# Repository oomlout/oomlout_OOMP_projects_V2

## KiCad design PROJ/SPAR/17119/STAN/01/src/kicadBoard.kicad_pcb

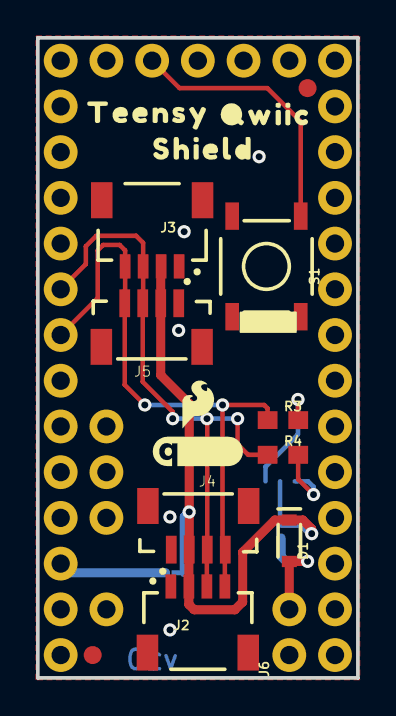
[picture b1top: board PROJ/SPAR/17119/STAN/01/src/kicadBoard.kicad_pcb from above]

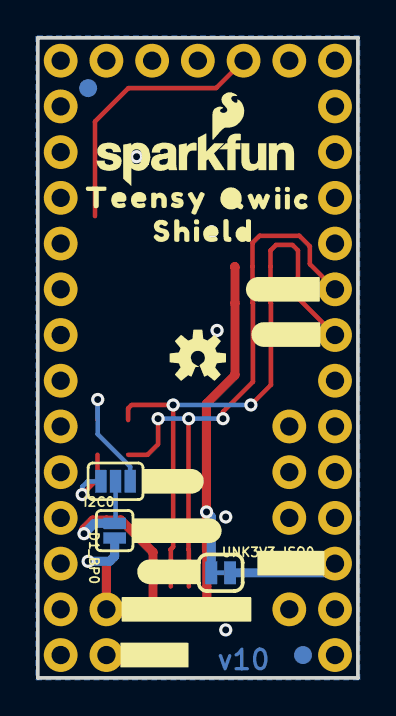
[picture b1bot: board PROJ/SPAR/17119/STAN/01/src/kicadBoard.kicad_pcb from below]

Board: 2 copper layers, 17.8 x 35.6 mm, 38 parts (18 on the bottom side), 9 nets.

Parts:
D1: 3A/10V/280mV; SOD-323
D1_BP0: SMT-JUMPER_2_NO_SILK
FD1, FD2, FD3, FD4: FIDUCIAL1X2; FIDUCIAL-1X2
FRAME1: FRAME-LETTER; CREATIVE_COMMONS
I2C0: JUMPER-SMT_3_NO_SILK; SMT-JUMPER_3_NO_SILK
J1: TEENSY; TEENSY_NOSILK
J2, J3: QWIIC_RA; JST04_1MM_RA
J4, J5: QWIIC_Vertical; JST04_1MM_VERT
J6: ALT PWR; 1X02_NO_SILK
LOGO1: SFE_LOGO_NAME_FLAME.1_INCH; SFE_LOGO_NAME_FLAME_.1
LOGO2: SFE_LOGO_FLAME.1_INCH; SFE_LOGO_FLAME_.1
LOGO3: OSHW-LOGOS; OSHW-LOGO-S
LOGO4: QWIIC_LOGO_5MM; QWIIC_5MM
R3, R4: 4.7k; 0603
S1: SMD_5.2MM; TACTILE_SWITCH_SMD_5.2MM
U$1: #I2C#0
U$2, U$13: TEENSY0
U$3: 3V36
U$4: #D1_BP#0
U$5: #ALT_3V3#0
U$6: #PRG#0
U$7: #GND#0
U$8, U$12: SHIELD0
U$9, U$11: QWIIC0
U$10: #ISO#0
U$15: #3V3#0
U$18: #SDA#0
U$19: #SCL#0
UNK3V3_ISO0: SMT-JUMPER_2_NC_TRACE_SILK

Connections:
3.3V: D1.C, D1_BP0.2, I2C0.2, J2.2, J3.2, J4.2, J5.2, UNK3V3_ISO0.1
GND: J1.AGND, J1.GND, J1.GND1, J2.1, J3.1, J4.1, J5.1, J6.1, S1.3
unnamed: I2C0.3, R4.2
unnamed: I2C0.1, R3.2
unnamed: J1.3V, UNK3V3_ISO0.2
unnamed: D1.A, D1_BP0.1, J6.2
unnamed: J1.PROG, S1.1
SCL: J1.19, J2.4, J3.4, J4.4, J5.4, R3.1
SDA: J1.18, J2.3, J3.3, J4.3, J5.3, R4.1

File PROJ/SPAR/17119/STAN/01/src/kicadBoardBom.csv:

"Id";"Designator";"Package";"Quantity";"Designation";"Supplier and ref";
1;"LOGO2";"SFE_LOGO_FLAME_.1";1;"SFE_LOGO_FLAME.1_INCH";;;
2;"J4,J5";"JST04_1MM_VERT";2;"QWIIC_Vertical";;;
3;"U$9,U$11";"QWIIC0";2;"";;;
4;"U$13,U$2";"TEENSY0";2;"";;;
5;"U$6";"#PRG#0";1;"";;;
6;"J1";"TEENSY_NOSILK";1;"TEENSY";;;
7;"FRAME1";"CREATIVE_COMMONS";1;"FRAME-LETTER";;;
8;"R4,R3";"0603";2;"4.7k";;;
9;"U$8,U$12";"SHIELD0";2;"";;;
10;"U$3";"3V36";1;"";;;
11;"D1";"SOD-323";1;"3A/10V/280mV";;;
12;"J3,J2";"JST04_1MM_RA";2;"QWIIC_RA";;;
13;"LOGO4";"QWIIC_5MM";1;"QWIIC_LOGO_5MM";;;
14;"FD3,FD1,FD2,FD4";"FIDUCIAL-1X2";4;"FIDUCIAL1X2";;;
15;"S1";"TACTILE_SWITCH_SMD_5.2MM";1;"SMD_5.2MM";;;
16;"J6";"1X02_NO_SILK";1;"ALT PWR";;;
17;"U$1";"#I2C#0";1;"";;;
18;"UNK3V3_ISO0";"SMT-JUMPER_2_NC_TRACE_SILK";1;"";;;
19;"U$7";"#GND#0";1;"";;;
20;"LOGO3";"OSHW-LOGO-S";1;"OSHW-LOGOS";;;
21;"U$10";"#ISO#0";1;"";;;
22;"D1_BP0";"SMT-JUMPER_2_NO_SILK";1;"";;;
23;"U$15";"#3V3#0";1;"";;;
24;"LOGO1";"SFE_LOGO_NAME_FLAME_.1";1;"SFE_LOGO_NAME_FLAME.1_INCH";;;
25;"U$18";"#SDA#0";1;"";;;
26;"U$5";"#ALT_3V3#0";1;"";;;
27;"U$19";"#SCL#0";1;"";;;
28;"U$4";"#D1_BP#0";1;"";;;
29;"I2C0";"SMT-JUMPER_3_NO_SILK";1;"JUMPER-SMT_3_NO_SILK";;;

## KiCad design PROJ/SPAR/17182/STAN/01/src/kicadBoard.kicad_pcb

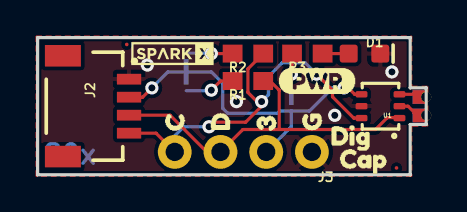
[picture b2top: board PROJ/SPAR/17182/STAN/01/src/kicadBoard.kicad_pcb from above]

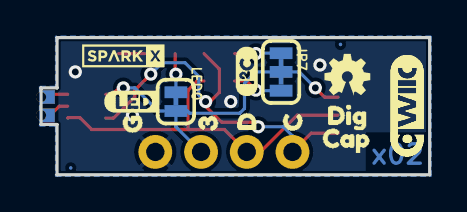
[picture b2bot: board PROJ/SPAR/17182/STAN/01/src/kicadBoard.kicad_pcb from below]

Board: 2 copper layers, 21.6 x 7.6 mm, 36 parts (16 on the bottom side), 10 nets.

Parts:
D1: RED; LED-0603
FRAME1: FRAME-LETTER; CREATIVE_COMMONS
J1: CONN_02_0603; 0603_CASTELLATED
J2: QWIIC_RIGHT_ANGLE; JST04_1MM_RA
J3: PTH; 1X04_NO_SILK
JP1, JP2, JP5, JP6: FIDUCIAL0.2MM; FIDUCIAL-0.2MM
JP7: JUMPER-SMT_3_2-NC_TRACE_SILK; SMT-JUMPER_3_2-NC_TRACE_SILK
LED0: JUMPER-SMT_2_NC_TRACE_SILK; SMT-JUMPER_2_NC_TRACE_SILK
LOGO1: OSHW-LOGOMINI; OSHW-LOGO-MINI
LOGO2: SPECIAL_INSTRUCTIONS-ORDERING; ORDERING_INSTRUCTIONS
R1, R2: 2.2k; 0603
R3: 1k; 0603
U1: NCD2400MDFN; DFN6
U$1: PWR2
U$3, U$7: 32
U$4, U$8: C0
U$5, U$13: D1
U$6, U$14: G3
U$9: I_SUPER2_C-()-03
U$11, U$18: CAP1
U$12, U$16: SPARKX-TINY
U$15: LED0
U$20, U$21: QWIIC_COPYRIGHT_SMALL
U$22, U$23: DIG0

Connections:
3.3V: J2.2, J3.2, JP7.2, LED0.2, U1.4
CN: J1.2, U1.3
CP: J1.1, U1.2
GND: D1.C, J2.1, J3.1, U1.5
unnamed: JP7.3, R1.2
unnamed: JP7.1, R2.2
unnamed: D1.A, R3.1
unnamed: LED0.1, R3.2
SCL: J2.4, J3.4, R2.1, U1.6
SDA: J2.3, J3.3, R1.1, U1.1

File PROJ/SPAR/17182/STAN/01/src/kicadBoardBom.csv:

"Id";"Designator";"Package";"Quantity";"Designation";"Supplier and ref";
1;"LOGO2";"ORDERING_INSTRUCTIONS";1;"SPECIAL_INSTRUCTIONS-ORDERING";;;
2;"J1";"0603_CASTELLATED";1;"CONN_02_0603";;;
3;"U$11,U$18";"CAP1";2;"";;;
4;"J3";"1X04_NO_SILK";1;"PTH";;;
5;"J2";"JST04_1MM_RA";1;"QWIIC_RIGHT_ANGLE";;;
6;"U$13,U$5";"D1";2;"";;;
7;"R2,R1";"0603";2;"2.2k";;;
8;"U$1";"PWR2";1;"";;;
9;"U1";"DFN6";1;"NCD2400MDFN";;;
10;"U$22,U$23";"DIG0";2;"";;;
11;"U$12,U$16";"SPARKX-TINY";2;"";;;
12;"D1";"LED-0603";1;"RED";;;
13;"JP2,JP6,JP1,JP5";"FIDUCIAL-0.2MM";4;"FIDUCIAL0.2MM";;;
14;"U$7,U$3";"32";2;"";;;
15;"R3";"0603";1;"1k";;;
16;"U$14,U$6";"G3";2;"";;;
17;"FRAME1";"CREATIVE_COMMONS";1;"FRAME-LETTER";;;
18;"U$8,U$4";"C0";2;"";;;
19;"LED0";"SMT-JUMPER_2_NC_TRACE_SILK";1;"JUMPER-SMT_2_NC_TRACE_SILK";;;
20;"U$21,U$20";"QWIIC_COPYRIGHT_SMALL";2;"";;;
21;"U$9";"I_SUPER2_C-()-03";1;"";;;
22;"JP7";"SMT-JUMPER_3_2-NC_TRACE_SILK";1;"JUMPER-SMT_3_2-NC_TRACE_SILK";;;
23;"LOGO1";"OSHW-LOGO-MINI";1;"OSHW-LOGOMINI";;;
24;"U$15";"LED0";1;"";;;

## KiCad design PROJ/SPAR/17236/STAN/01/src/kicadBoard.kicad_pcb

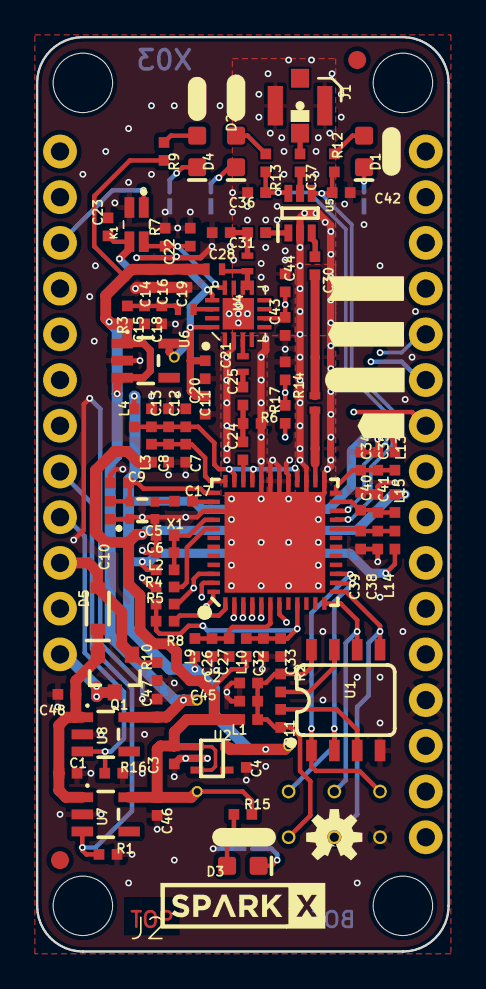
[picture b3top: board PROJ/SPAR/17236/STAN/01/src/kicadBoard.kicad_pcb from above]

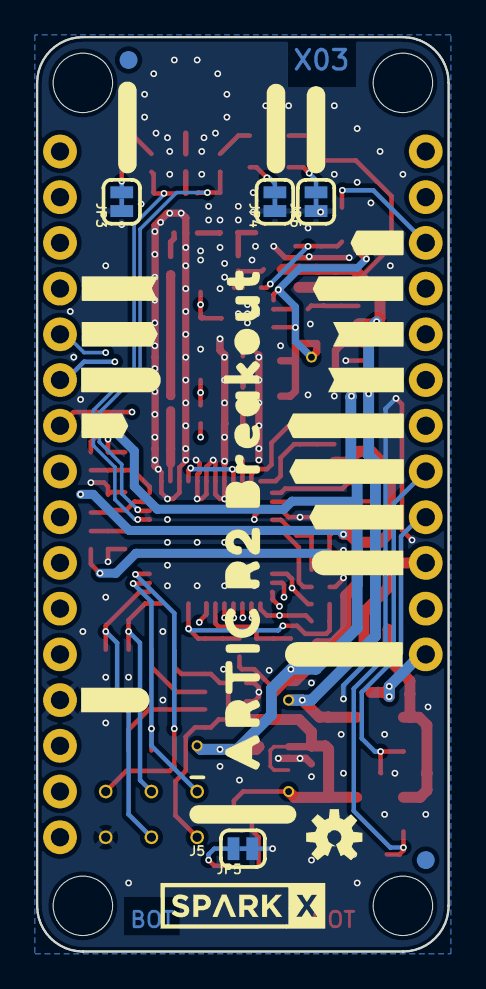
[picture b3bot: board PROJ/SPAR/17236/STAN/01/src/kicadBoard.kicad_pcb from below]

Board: 4 copper layers, 22.9 x 50.8 mm, 144 parts (28 on the bottom side), 65 nets.

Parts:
C1, C15, C16, C20, C44, C46, C47: 2.2uF; 0402-TIGHT
C2, C5, C7, C18, C27, C33, C34, C39, C40: 22pF; 0402-TIGHT
C3, C4, C9, C12: 1.0uF; 0402-TIGHT
C6, C8, C26, C32, C35, C38, C41, C45, C48: 0.1uF; 0402-TIGHT
C10: 47nF; 0402-TIGHT
C11, C19, C21, C22, C23, C24, C25, C30, C31, C36, C37, C42, C43: 100pF; 0402-TIGHT
C13, C14: 10uF; 0402-TIGHT
C17: 1.0nF; 0402-TIGHT
C28: 9.1pF; 0402-TIGHT
C29: 2.4 pF; 0402_MURATA
D1, D2: Yellow; LED-0603
D3, D4: RED; LED-0603
D5: 1A/23V/620mV; SOD-323
FD1, FD2, FD3, FD4: FIDUCIAL1X2; FIDUCIAL-1X2
FRAME1: FRAME-LEDGER; CREATIVE_COMMONS
J1: U.FL
J2: THING_PLUS
J5: Flash Programming; 2X3_TEST_POINTS
JP3, JP4, JP5, JP6: JUMPER-SMT_2_NC_TRACE_SILK; SMT-JUMPER_2_NC_TRACE_SILK
K1: TLP3475R; TLP3475RTPF
L1, L2, L3, L4, L9, L10, L13, L14, L15: 30Ω; 0402-TIGHT
L5: 15nH; 0402_COILCRAFT
L6: 27nH; 0402_COILCRAFT
L7: 18nH; 0402_COILCRAFT
L8: 12nH; 0402_COILCRAFT
L11: 30nH; 0402_COILCRAFT
L12: 51nH; 0402_COILCRAFT
LOGO1: SPECIAL_INSTRUCTIONS-ORDERING; ORDERING_INSTRUCTIONS
LOGO2, LOGO3: OSHW-LOGOS; OSHW-LOGO-S
Q1: 3.1A/30V/105mΩ; SOT23-3
R1, R7, R16: 10k; 0402-TIGHT
R2, R11: 0; 0402-TIGHT
R3: 3.9; 0402-TIGHT
R4: 33k; 0402-TIGHT
R5, R8, R10: 100k; 0402-TIGHT
R6: 220; 0402-TIGHT
R9, R12, R13, R15: 1k; 0402-TIGHT
R14: 470; 0402-TIGHT
R17: 47; 0402-TIGHT
SPARKX1, SPARKX2: SPARKX-LOGO4; SPARKX-MEDIUM
TP1, TP2, TP3, TP4: TEST-POINTTP_15TH_THRU; TP_15TH
U1: 2Mbit SPI Flash; SO08
U2: 1.8V/100mA; SC70
U3: ARTIC_R2; QFN-48
U4: RFPA0133; QFN50P300X300X86-17N
U5: AS179-92LF; SOT65P220X100-6N
U6: 3.0V; SOT23-5
U7, U8: 3.3V; SOT23-5
U$1: #TX#0
U$2: #RX#0
U$3: #RX_LED#0
U$4: #TX_LED#0
U$5: #RF_LED#0
U$6: #G8#0
U$7: #RF#0
U$8: #RF_EN#0
U$9: CIPO#0
U$10: #CIPO0
U$11: #COPI0
U$12: COPI#0
U$13: #SCLK0
U$14: SCLK#0
U$15: #CS0
U$16: CS#0
U$17: GND#0
U$18: #RESETB0
U$19: #PWR_EN0
U$20: #VBATT#0
U$21: #VUSB#0
U$24: #BOOT0
U$25: #INT10
U$26: #INT20
U$27: #PWR_LED#0
U$28: #PWR#0
U$29: ARTIC_R2_BREAKOUT0
X1: CRYSTAL-TCXO-26MHZ; CRYSTAL-TCXO-SMD-1.65X1.25

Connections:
1.8V: C4.1, L2.2, L4.2, L9.2, L13.2, L14.2, TP3.P$1, U2.5
ANTENNA: C37.1, J1.FEED
ARTIC_PWR_EN: J2.8, R1.2, U7.3
BOOT: J2.4, R5.1, U3.46
CIPO: J2.16, U3.5
COPI: J2.17, U3.4
CS: J2.19, U3.2
FLSH_CEN: J5.5, U1.1, U3.15
FLSH_SCLK: J5.3, U1.6, U3.12
FLSH_SI: J5.4, U1.5, U3.13
FLSH_SO: J5.1, U1.2, U3.14
FLSH_VCC: C2.1, C45.1, J5.2, L1.1, R2.2, R11.2, U1.8
G8: J2.3, K1.1
GND: C1.2, C2.2, C3.2, C4.2, C5.2, C6.2, C7.2, C8.2, C9.2, C10.2, C11.2, C12.2, C13.2, C14.2, C15.2, C16.2, C18.2, C19.2, C20.1, C21.1, C22.1, C23.2, C26.2, C27.2, C28.1, C32.2, C33.2, C34.2, C35.2, C36.2, C38.2, C39.2, C40.2, C41.2, C42.2, C43.1, C44.2, C45.2, C46.2, C47.2, C48.2, J1.1, J1.2, J2.25, J5.6, JP3.1, JP4.1, JP5.1, JP6.1, K1.2, L11.P$1, L12.P$1, R1.1, R4.2, R6.1, R7.2, R10.1, R14.1, R16.1, U1.4, U2.2, U3.25, U3.27, U3.29, U3.30, U3.31, U3.32, U3.39, U3.GND, U4.2, U4.EDAP, U5.2, U6.2, U7.2, U8.2, X1.1, X1.2
INT1: J2.5, U3.47
INT2: J2.6, U3.48
unnamed: R2.1, U1.7
unnamed: R11.1, U1.3
unnamed: C34.1, C35.1, L13.1, U3.24
unnamed: C40.1, C41.1, L15.1, U3.23
unnamed: D2.A, R13.1
unnamed: D1.A, R12.1
unnamed: C26.1, C27.1, L9.1, U3.6
unnamed: C32.1, C33.1, L10.1, R5.2, R8.1, U3.9
unnamed: C11.1, C12.1, C13.1, L4.1, U3.28, U3.33, U3.35
unnamed: C7.1, C8.1, L3.1, U3.36
unnamed: R4.1, U3.41
unnamed: C5.1, C6.1, L2.1, U3.40
unnamed: C9.1, C10.1, U3.37, X1.4
unnamed: C17.1, X1.3
unnamed: C17.2, U3.38
unnamed: C24.1, U3.34
unnamed: C24.2, C25.1, R6.2
unnamed: L5.P$2, U4.14
unnamed: C15.1, C18.1, L5.P$1, R3.1
unnamed: C29.P$1, L11.P$2, U3.26
unnamed: D4.A, R9.1
unnamed: C25.2, L7.P$1
unnamed: L7.P$2, U4.3
unnamed: L6.P$2, L8.P$1, U4.9, U4.10
unnamed: D4.C, JP6.2
unnamed: C31.1, U5.1
unnamed: C30.1, U5.3
unnamed: C37.2, U5.5
unnamed: C38.1, C39.1, L14.1, U3.20
unnamed: D1.C, JP3.2
unnamed: D2.C, JP4.2
unnamed: D3.A, R15.1
unnamed: D3.C, JP5.2
PA_PD: R17.1, U3.7
PD: C43.2, C44.1, R14.2, R17.2, U4.6
RESETB: J2.7, R8.2, U3.1
RFG8: C22.2, K1.4, R7.1, U4.12
RF_PWR_EN: J2.9, R16.2, U8.3
RF_RX: C29.P$2, C30.2, L12.P$2
RF_TX: C28.2, C31.2, L8.P$2
RXSW: C36.1, R13.2, U3.22, U5.6
SCLK: J2.18, U3.3
TXSW: C42.1, R12.2, U3.21, U5.4
VDD: C3.1, C46.1, L1.2, L3.2, L10.2, L15.2, R15.2, TP1.P$1, U2.1, U2.3, U7.5
VDDA: C14.1, C16.1, C19.1, C47.1, L6.P$1, R3.2, R9.2, TP2.P$1, U6.1, U6.3, U8.5
VIN: C1.1, C48.1, D5.C, Q1.2, U7.1, U8.1
VREF1: C20.2, C21.2, C23.1, K1.3, TP4.P$1, U4.13, U4.16, U6.5
V_BATT: J2.12, Q1.3
V_USB: D5.A, J2.10, Q1.1, R10.2

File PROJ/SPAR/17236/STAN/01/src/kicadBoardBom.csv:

"Id";"Designator";"Package";"Quantity";"Designation";"Supplier and ref";
1;"R13,R9,R15,R12";"0402-TIGHT";4;"1k";;;
2;"U$11";"#COPI0";1;"";;;
3;"R8,R5,R10";"0402-TIGHT";3;"100k";;;
4;"R3";"0402-TIGHT";1;"3.9";;;
5;"X1";"CRYSTAL-TCXO-SMD-1.65X1.25";1;"CRYSTAL-TCXO-26MHZ";;;
6;"L8";"0402_COILCRAFT";1;"12nH";;;
7;"R11,R2";"0402-TIGHT";2;"0";;;
8;"C8,C32,C26,C6,C41,C35,C48,C45,C38";"0402-TIGHT";9;"0.1uF";;;
9;"TP1,TP2,TP3,TP4";"TP_15TH";4;"TEST-POINTTP_15TH_THRU";;;
10;"SPARKX1,SPARKX2";"SPARKX-MEDIUM";2;"SPARKX-LOGO4";;;
11;"L9,L14,L1,L3,L10,L2,L4,L13,L15";"0402-TIGHT";9;"30Ω";;;
12;"D3,D4";"LED-0603";2;"RED";;;
13;"C43,C42,C36,C37,C22,C31,C19,C21,C23,C25,C24,C30,C11";"0402-TIGHT";13;"100pF";;;
14;"C27,C7,C34,C5,C33,C2,C39,C18,C40";"0402-TIGHT";9;"22pF";;;
15;"C20,C16,C15,C46,C47,C1,C44";"0402-TIGHT";7;"2.2uF";;;
16;"U5";"SOT65P220X100-6N";1;"AS179-92LF";;;
17;"LOGO2,LOGO3";"OSHW-LOGO-S";2;"OSHW-LOGOS";;;
18;"U$13";"#SCLK0";1;"";;;
19;"R7,R1,R16";"0402-TIGHT";3;"10k";;;
20;"K1";"TLP3475RTPF";1;"TLP3475R";;;
21;"U6";"SOT23-5";1;"3.0V";;;
22;"C4,C9,C3,C12";"0402-TIGHT";4;"1.0uF";;;
23;"L11";"0402_COILCRAFT";1;"30nH";;;
24;"FRAME1";"CREATIVE_COMMONS";1;"FRAME-LEDGER";;;
25;"U$10";"#CIPO0";1;"";;;
26;"R6";"0402-TIGHT";1;"220";;;
27;"U$28";"#PWR#0";1;"";;;
28;"Q1";"SOT23-3";1;"3.1A/30V/105mΩ";;;
29;"U$1";"#TX#0";1;"";;;
30;"R14";"0402-TIGHT";1;"470";;;
31;"D5";"SOD-323";1;"1A/23V/620mV";;;
32;"U1";"SO08";1;"2Mbit SPI Flash";;;
33;"J2";"THING_PLUS";1;"THING_PLUS";;;
34;"R4";"0402-TIGHT";1;"33k";;;
35;"C14,C13";"0402-TIGHT";2;"10uF";;;
36;"L5";"0402_COILCRAFT";1;"15nH";;;
37;"FD1,FD3,FD4,FD2";"FIDUCIAL-1X2";4;"FIDUCIAL1X2";;;
38;"C10";"0402-TIGHT";1;"47nF";;;
39;"C29";"0402_MURATA";1;"2.4 pF";;;
40;"L7";"0402_COILCRAFT";1;"18nH";;;
41;"LOGO1";"ORDERING_INSTRUCTIONS";1;"SPECIAL_INSTRUCTIONS-ORDERING";;;
42;"U4";"QFN50P300X300X86-17N";1;"RFPA0133";;;
43;"D1,D2";"LED-0603";2;"Yellow";;;
44;"L6";"0402_COILCRAFT";1;"27nH";;;
45;"C17";"0402-TIGHT";1;"1.0nF";;;
46;"L12";"0402_COILCRAFT";1;"51nH";;;
47;"U8,U7";"SOT23-5";2;"3.3V";;;
48;"C28";"0402-TIGHT";1;"9.1pF";;;
49;"U$15";"#CS0";1;"";;;
50;"U$2";"#RX#0";1;"";;;
51;"J1";"U.FL";1;"U.FL";;;
52;"U3";"QFN-48";1;"ARTIC_R2";;;
53;"U2";"SC70";1;"1.8V/100mA";;;
54;"R17";"0402-TIGHT";1;"47";;;
55;"U$7";"#RF#0";1;"";;;
56;"U$4";"#TX_LED#0";1;"";;;
57;"U$8";"#RF_EN#0";1;"";;;
58;"JP5,JP6,JP3,JP4";"SMT-JUMPER_2_NC_TRACE_SILK";4;"JUMPER-SMT_2_NC_TRACE_SILK";;;
59;"U$14";"SCLK#0";1;"";;;
60;"U$16";"CS#0";1;"";;;
61;"U$25";"#INT10";1;"";;;
62;"U$5";"#RF_LED#0";1;"";;;
63;"U$29";"ARTIC_R2_BREAKOUT0";1;"";;;
64;"U$19";"#PWR_EN0";1;"";;;
65;"U$12";"COPI#0";1;"";;;
66;"U$26";"#INT20";1;"";;;
67;"U$3";"#RX_LED#0";1;"";;;
68;"U$17";"GND#0";1;"";;;
69;"U$6";"#G8#0";1;"";;;
70;"U$18";"#RESETB0";1;"";;;
71;"J5";"2X3_TEST_POINTS";1;"Flash Programming";;;
72;"U$21";"#VUSB#0";1;"";;;
73;"U$9";"CIPO#0";1;"";;;
74;"U$24";"#BOOT0";1;"";;;
75;"U$20";"#VBATT#0";1;"";;;
76;"U$27";"#PWR_LED#0";1;"";;;

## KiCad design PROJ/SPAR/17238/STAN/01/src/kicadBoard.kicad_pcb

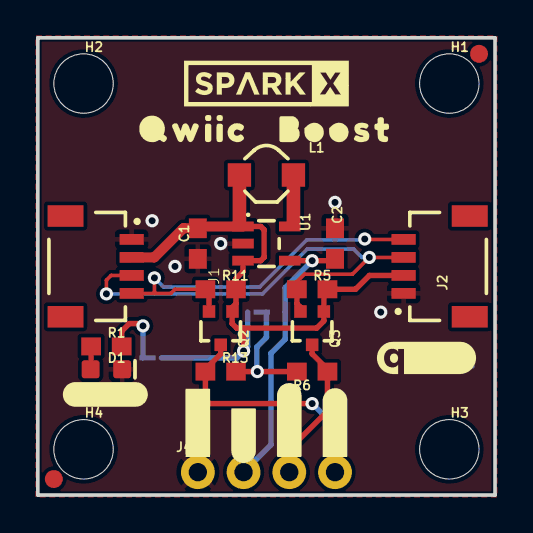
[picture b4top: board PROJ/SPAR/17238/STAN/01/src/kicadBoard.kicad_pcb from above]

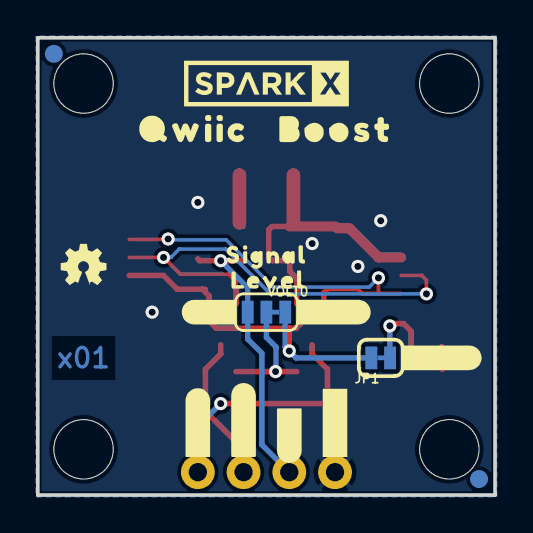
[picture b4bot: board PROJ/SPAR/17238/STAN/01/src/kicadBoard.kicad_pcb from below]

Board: 2 copper layers, 25.4 x 25.4 mm, 48 parts (17 on the bottom side), 11 nets.

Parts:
C1: 4.7uF; 0603
C2: 10uF; 0603
D1: RED; LED-0603
FD1, FD2, FD3, FD4: FIDUCIAL1X2; FIDUCIAL-1X2
FRAME1: FRAME-LETTER; CREATIVE_COMMONS
H1, H2, H3, H4: STAND-OFF
J1, J2: QWIIC_RIGHT_ANGLE; JST04_1MM_RA
J4: 1X04_NO_SILK
JP1: SMT-JUMPER_2_NC_TRACE_SILK
L1: 4.7µH/±30%/1.2A; INDUCTOR_4.7UH
LOGO1: QWIIC_LOGO_CONNECTOR; QWIIC_5.5MM
LOGO2: OSHW-LOGOMINI; OSHW-LOGO-MINI
Q2, Q3: 310mA/60V/1.6Ω; SOT323
R1: 1k; 0603
R5, R6, R11, R13: 2.2k; 0603
U1: XC9140; SOT23-5
U$1, U$2, U$14: #5V#3
U$3, U$4: #GND#0
U$5: #PWR#4
U$6, U$10: #SCL#2
U$7, U$9: #SDA#1
U$8, U$20: SPARKX-LOGO4; SPARKX-MEDIUM
U$11, U$19: BOOST1
U$12, U$18: QWIIC0
U$13: #3V3#2
U$15: #PWR#0
U$16: LEVEL1
U$17: SIGNAL0
VOLT0: SMT-JUMPER_3_1-NC_TRACE_SILK

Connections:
3.3V: C1.2, J1.2, J2.2, JP1.2, L1.P$2, Q2.1, Q3.1, R5.2, R11.2, U1.1, U1.3, VOLT0.3
5V: C2.2, J4.2, U1.4, VOLT0.1
GND: C1.1, C2.1, D1.C, J1.1, J2.1, J4.1, U1.2
HV_SCL: J4.4, Q2.3, R13.1
HV_SDA: J4.3, Q3.3, R6.1
unnamed: D1.A, R1.1
unnamed: L1.P$1, U1.5
unnamed: JP1.1, R1.2
SCL: J1.4, J2.4, Q2.2, R11.1
SDA: J1.3, J2.3, Q3.2, R5.1
VCC: R6.2, R13.2, VOLT0.2

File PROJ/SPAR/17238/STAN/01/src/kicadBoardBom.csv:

"Id";"Designator";"Package";"Quantity";"Designation";"Supplier and ref";
1;"R11,R13,R5,R6";"0603";4;"2.2k";;;
2;"U$6,U$10";"#SCL#2";2;"";;;
3;"U$7,U$9";"#SDA#1";2;"";;;
4;"H3,H1,H4,H2";"STAND-OFF";4;"STAND-OFF";;;
5;"U$8,U$20";"SPARKX-MEDIUM";2;"SPARKX-LOGO4";;;
6;"U$4,U$3";"#GND#0";2;"";;;
7;"U1";"SOT23-5";1;"XC9140";;;
8;"C2";"0603";1;"10uF";;;
9;"FRAME1";"CREATIVE_COMMONS";1;"FRAME-LETTER";;;
10;"LOGO1";"QWIIC_5.5MM";1;"QWIIC_LOGO_CONNECTOR";;;
11;"U$11,U$19";"BOOST1";2;"";;;
12;"U$12,U$18";"QWIIC0";2;"";;;
13;"D1";"LED-0603";1;"RED";;;
14;"R1";"0603";1;"1k";;;
15;"J2,J1";"JST04_1MM_RA";2;"QWIIC_RIGHT_ANGLE";;;
16;"U$5";"#PWR#4";1;"";;;
17;"Q2,Q3";"SOT323";2;"310mA/60V/1.6Ω";;;
18;"FD3,FD1,FD2,FD4";"FIDUCIAL-1X2";4;"FIDUCIAL1X2";;;
19;"C1";"0603";1;"4.7uF";;;
20;"J4";"1X04_NO_SILK";1;"";;;
21;"L1";"INDUCTOR_4.7UH";1;"4.7µH/±30%/1.2A";;;
22;"U$1,U$2,U$14";"#5V#3";3;"";;;
23;"JP1";"SMT-JUMPER_2_NC_TRACE_SILK";1;"";;;
24;"U$16";"LEVEL1";1;"";;;
25;"U$13";"#3V3#2";1;"";;;
26;"U$15";"#PWR#0";1;"";;;
27;"U$17";"SIGNAL0";1;"";;;
28;"VOLT0";"SMT-JUMPER_3_1-NC_TRACE_SILK";1;"";;;
29;"LOGO2";"OSHW-LOGO-MINI";1;"OSHW-LOGOMINI";;;

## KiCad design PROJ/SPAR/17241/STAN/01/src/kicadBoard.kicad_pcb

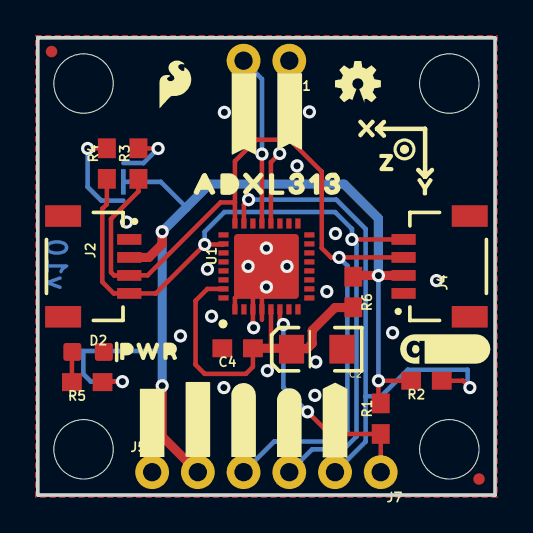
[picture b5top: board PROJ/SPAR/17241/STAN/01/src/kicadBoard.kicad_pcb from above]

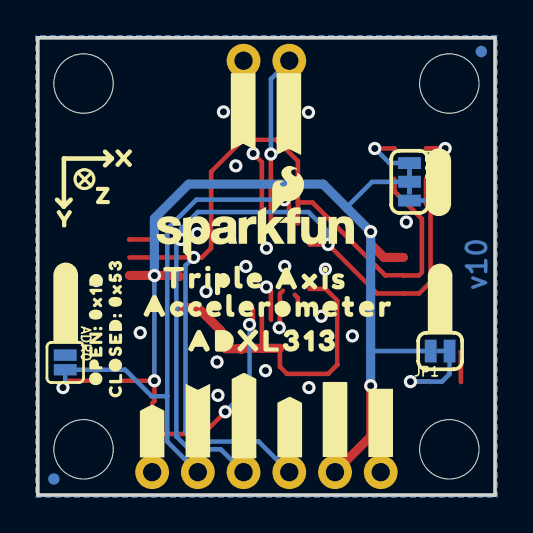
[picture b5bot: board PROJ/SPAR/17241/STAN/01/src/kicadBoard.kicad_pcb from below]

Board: 2 copper layers, 25.4 x 25.4 mm, 63 parts (26 on the bottom side), 13 nets.

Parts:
ADR0: SMT-JUMPER_2_NO_SILK
C2: 10uF; EIA3216
C4: 0.1uF; 0603
D2: RED; LED-0603
FRAME1: FRAME-LETTER; CREATIVE_COMMONS
I2C0: SMT-JUMPER_3_2-NC_TRACE_SILK
J1, J7: 1X02_NO_SILK
J2, J4: QWIIC_RA; JST04_1MM_RA
J5: 1X04_NO_SILK
JP1: LED; SMT-JUMPER_2_NC_TRACE_SILK
JP2, JP5, JP6, JP11: FIDUCIALUFIDUCIAL; MICRO-FIDUCIAL
JP3, JP4, JP8, JP9: STAND-OFF
LOGO1: OSHW-LOGOMINI; OSHW-LOGO-MINI
LOGO2: SFE_LOGO_NAME_FLAME.1_INCH; SFE_LOGO_NAME_FLAME_.1
LOGO3: SFE_LOGO_FLAME.1_INCH; SFE_LOGO_FLAME_.1
LOGO4: QWIIC_LOGO_5MM; QWIIC_5MM
R1, R2: 10k; 0603
R3, R4: 4.7k; 0603
R5: 1k; 0603
R6: 0; 0603
U1: ADXL313; LFCSP
U$1: TRIPLE0
U$2: AXIS0
U$3: ACCELEROMETER0
U$4, U$19: ADXL3130
U$5, U$6: #GND#0
U$7, U$8: #3#3V#0
U$9: #SDA#0
U$10: #SDI#0
U$11: #SCL#0
U$12: #_ADR#0
U$13, U$14: #INT2#0
U$15, U$16: #INT1#0
U$17, U$21: X0
U$18: ##CS##0
U$20: #SCLK#0
U$22: OPEN#_0X1D0
U$23: CLOSED#_0X530
U$24: #LED#0
U$25: PWR0
U$26, U$29: Y0
U$27: #I2C#0
U$28: #ADR#0
U$30: #SDO#0
U$31, U$32: Z0

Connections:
3.3V: I2C0.2, J2.2, J4.2, J5.2, JP1.2, R1.2, R2.2, R6.1
GND: ADR0.1, C2.C, C4.2, D2.C, J2.1, J4.1, J5.1, U1.1, U1.3, U1.4, U1.EPAD
INT1: J1.1, U1.20
INT2: J1.2, U1.21
unnamed: I2C0.1, R3.2
unnamed: I2C0.3, R4.2
unnamed: C2.A, C4.1, R6.2, U1.5, U1.31
unnamed: D2.A, R5.2
unnamed: JP1.1, R5.1
SCL: J2.4, J4.4, J5.4, R4.1, U1.26
SDA: J2.3, J4.3, J5.3, R3.1, U1.24
SDO/ADR: ADR0.2, J7.2, R2.1, U1.23
~CS: J7.1, R1.1, U1.6

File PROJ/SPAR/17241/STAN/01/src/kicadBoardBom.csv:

"Id";"Designator";"Package";"Quantity";"Designation";"Supplier and ref";
1;"U$9";"#SDA#0";1;"";;;
2;"R3,R4";"0603";2;"4.7k";;;
3;"J2,J4";"JST04_1MM_RA";2;"QWIIC_RA";;;
4;"JP9,JP4,JP3,JP8";"STAND-OFF";4;"STAND-OFF";;;
5;"U$25";"PWR0";1;"";;;
6;"U$28";"#ADR#0";1;"";;;
7;"LOGO4";"QWIIC_5MM";1;"QWIIC_LOGO_5MM";;;
8;"D2";"LED-0603";1;"RED";;;
9;"C4";"0603";1;"0.1uF";;;
10;"U1";"LFCSP";1;"ADXL313";;;
11;"JP2,JP6,JP11,JP5";"MICRO-FIDUCIAL";4;"FIDUCIALUFIDUCIAL";;;
12;"R1,R2";"0603";2;"10k";;;
13;"U$29,U$26";"Y0";2;"";;;
14;"R5";"0603";1;"1k";;;
15;"LOGO1";"OSHW-LOGO-MINI";1;"OSHW-LOGOMINI";;;
16;"U$11";"#SCL#0";1;"";;;
17;"LOGO3";"SFE_LOGO_FLAME_.1";1;"SFE_LOGO_FLAME.1_INCH";;;
18;"U$21,U$17";"X0";2;"";;;
19;"J5";"1X04_NO_SILK";1;"";;;
20;"U$5,U$6";"#GND#0";2;"";;;
21;"U$7,U$8";"#3#3V#0";2;"";;;
22;"U$32,U$31";"Z0";2;"";;;
23;"FRAME1";"CREATIVE_COMMONS";1;"FRAME-LETTER";;;
24;"R6";"0603";1;"0";;;
25;"U$13,U$14";"#INT2#0";2;"";;;
26;"J1,J7";"1X02_NO_SILK";2;"";;;
27;"U$19,U$4";"ADXL3130";2;"";;;
28;"C2";"EIA3216";1;"10uF";;;
29;"U$15,U$16";"#INT1#0";2;"";;;
30;"U$20";"#SCLK#0";1;"";;;
31;"ADR0";"SMT-JUMPER_2_NO_SILK";1;"";;;
32;"I2C0";"SMT-JUMPER_3_2-NC_TRACE_SILK";1;"";;;
33;"JP1";"SMT-JUMPER_2_NC_TRACE_SILK";1;"LED";;;
34;"U$12";"#_ADR#0";1;"";;;
35;"U$2";"AXIS0";1;"";;;
36;"LOGO2";"SFE_LOGO_NAME_FLAME_.1";1;"SFE_LOGO_NAME_FLAME.1_INCH";;;
37;"U$30";"#SDO#0";1;"";;;
38;"U$24";"#LED#0";1;"";;;
39;"U$18";"##CS##0";1;"";;;
40;"U$10";"#SDI#0";1;"";;;
41;"U$3";"ACCELEROMETER0";1;"";;;
42;"U$1";"TRIPLE0";1;"";;;
43;"U$23";"CLOSED#_0X530";1;"";;;
44;"U$27";"#I2C#0";1;"";;;
45;"U$22";"OPEN#_0X1D0";1;"";;;

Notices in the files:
parts and their libraries:
RELEASED UNDER THE CREATIVE COMMONS ATTRIBUTION SHARE-ALIKE 4.0 LICENSE
HTTPS://CREATIVECOMMONS.ORG/LICENSES/BY-SA/4.0
